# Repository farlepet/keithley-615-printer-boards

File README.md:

Keithley 615 Electrometer Printer Board Recreation
==================================================

This repo contains modern reproductions of the buffer/printer PCBs (PC209, PC218)
for the Keithley 615 electrometer.

Boards
------

 - PC218
   - Signal inverter/buffer board
   - Recreation of the origional PC218 schematic using modern SMD components is
     in the `PC218` directory
   - A simplified version using more modern ICs can be found in the `PC218v2` directory
 - PC209
   - Signal inverter/buffer and trigger board
   - Simplified version of the origional board can be found in the `PC209` directory
     - Same inverter/buffer scheme as PC218v2, with the origional trigger pulse
       generator and logic reduced down to discrete transistors, to simplify design.
 - Digital Interface Board
   - This will be a new board designed to connect to the 615 via the 50-pin
     Centronics connector
   - Planned features:
     - Passive data collection
     - Active triggering
     - USB-serial
     - RS-232 via DE-9
     - Ethernet

Photos
------

PC218 v2.2:

PC209 v1.0:

Interface/network board v1.0:

50-pin test board v1.0:

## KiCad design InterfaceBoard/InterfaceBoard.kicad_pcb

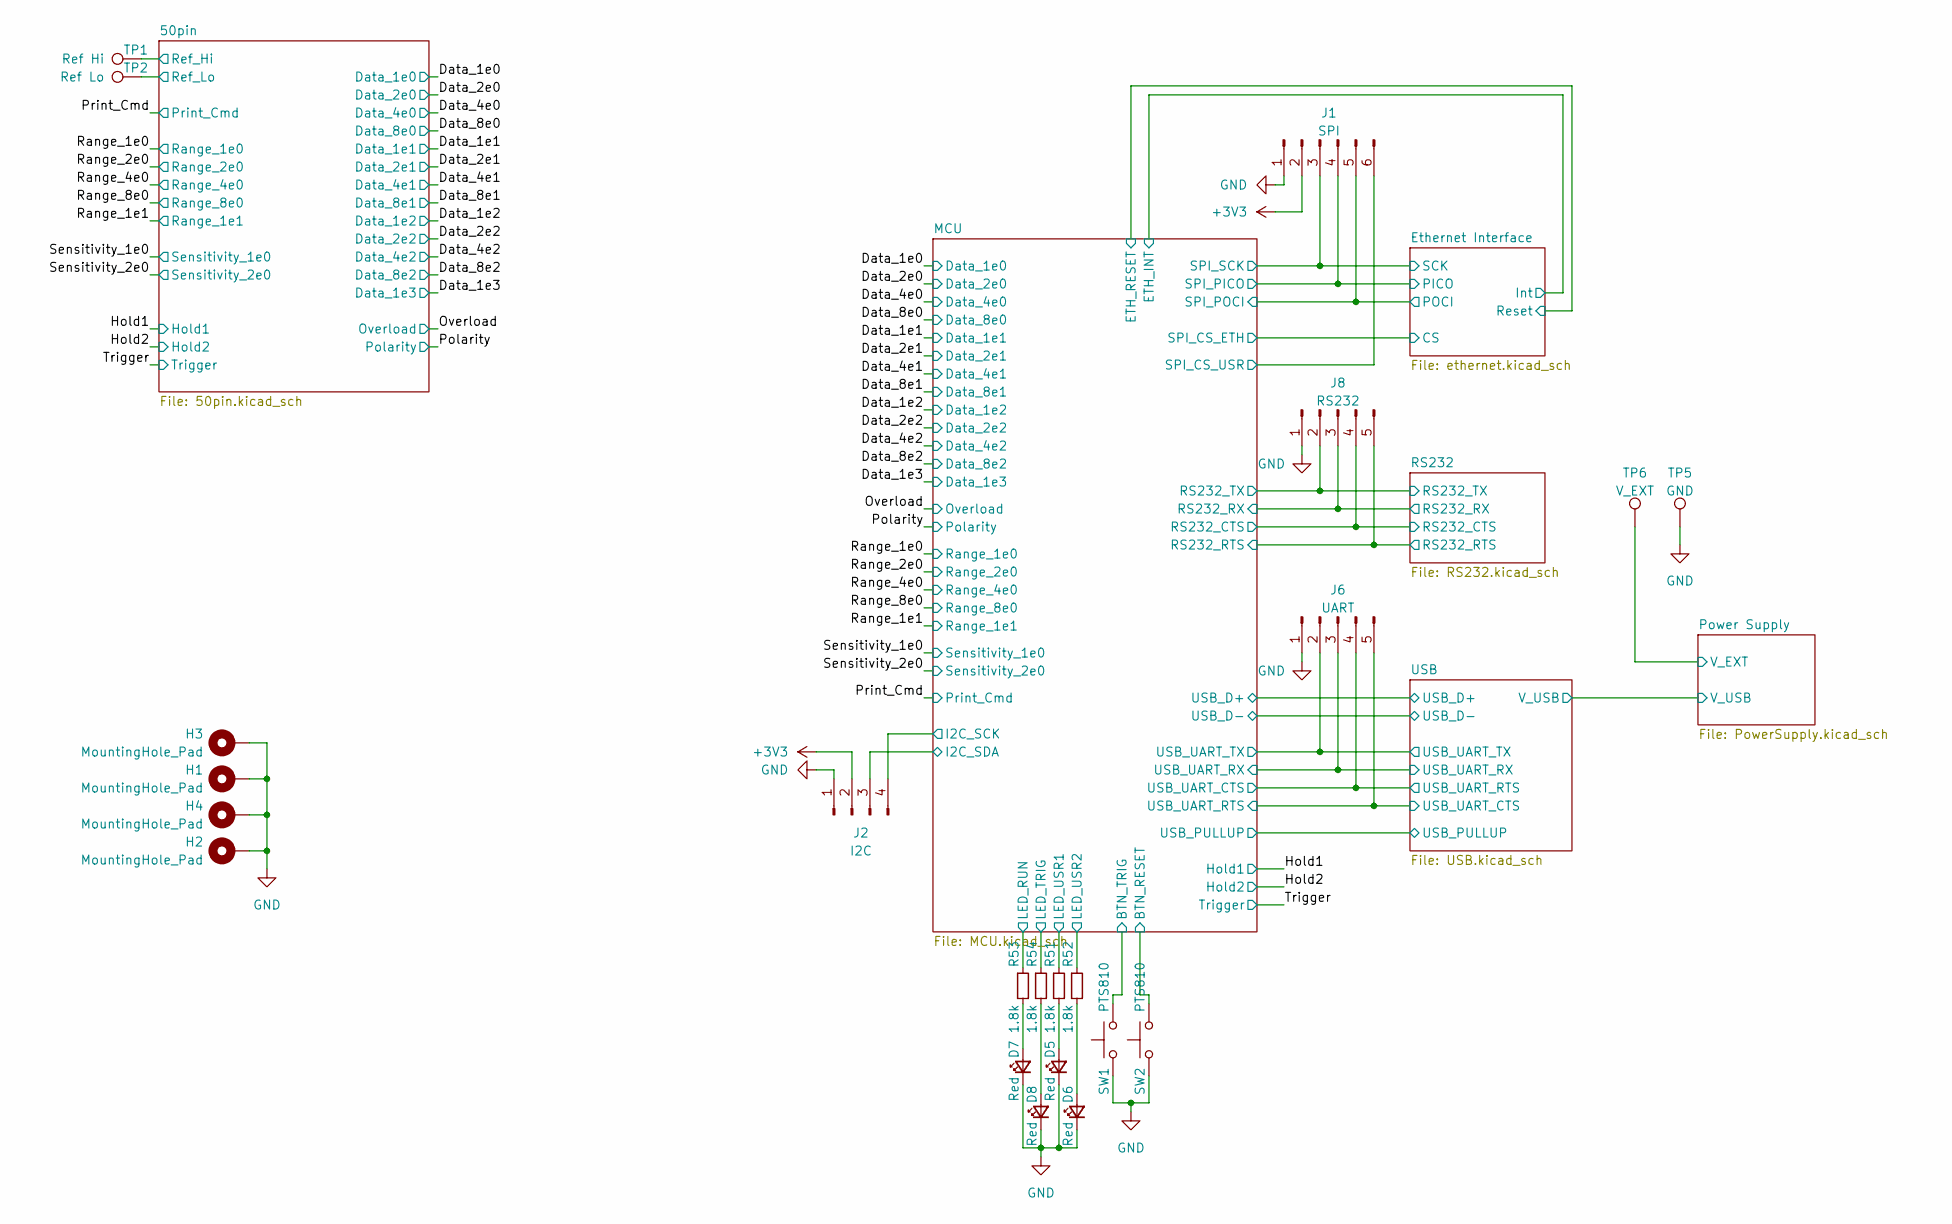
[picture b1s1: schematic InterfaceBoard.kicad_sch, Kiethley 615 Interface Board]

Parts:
D5, D6, D7, D8: Red; LED_0603_1608Metric
H1, H2, H3, H4: MountingHole_Pad; MountingHole_3.2mm_M3_Pad
J1: SPI; PinHeader_1x06_P1.27mm_Vertical
J2: I2C; PinHeader_1x04_P1.27mm_Vertical
J6: UART; PinHeader_1x05_P1.27mm_Vertical
J8: RS232; PinHeader_1x05_P1.27mm_Vertical
R51, R52, R53, R54: 1.8k; R_0603_1608Metric
SW1, SW2: PTS810; SW_SPST_PTS810
TP1: Ref Hi; TestPoint_Pad_1.5x1.5mm
TP2: Ref Lo; TestPoint_Pad_1.5x1.5mm
TP5: GND; TestPoint_THTPad_2.0x2.0mm_Drill1.0mm
TP6: V_EXT; TestPoint_THTPad_2.0x2.0mm_Drill1.0mm

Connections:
+3V3: J1.2, J2.2; also elsewhere on the board
/50pin/Ref_Hi: TP1.1; also elsewhere on the board
/50pin/Ref_Lo: TP2.1; also elsewhere on the board
/Ethernet Interface/PICO: J1.4; also elsewhere on the board
/Ethernet Interface/POCI: J1.5; also elsewhere on the board
/Ethernet Interface/SCK: J1.3; also elsewhere on the board
/MCU/BTN_TRIG: SW1.2; also elsewhere on the board
/MCU/I2C_SCK: J2.4; also elsewhere on the board
/MCU/I2C_SDA: J2.3; also elsewhere on the board
/MCU/LED_RUN: R53.1; also elsewhere on the board
/MCU/LED_TRIG: R54.1; also elsewhere on the board
/MCU/LED_USR1: R51.1; also elsewhere on the board
/MCU/LED_USR2: R52.1; also elsewhere on the board
/MCU/NRST: SW2.2; also elsewhere on the board
/MCU/RS232_CTS: J8.4; also elsewhere on the board
/MCU/RS232_RTS: J8.5; also elsewhere on the board
/MCU/RS232_RX: J8.3; also elsewhere on the board
/MCU/RS232_TX: J8.2; also elsewhere on the board
/MCU/SPI_CS_USR: J1.6; also elsewhere on the board
/MCU/USB_UART_CTS: J6.4; also elsewhere on the board
/MCU/USB_UART_RTS: J6.5; also elsewhere on the board
/MCU/USB_UART_RX: J6.3; also elsewhere on the board
/MCU/USB_UART_TX: J6.2; also elsewhere on the board
/Power Supply/V_EXT: TP6.1; also elsewhere on the board
GND: D5.1 (K), D6.1 (K), D7.1 (K), D8.1 (K), H1.1, H2.1, H3.1, H4.1, J1.1, J2.1, J6.1, J8.1, SW1.1, SW2.1, TP5.1; also elsewhere on the board
unnamed: D5.2 (A), R51.2
unnamed: D6.2 (A), R52.2
unnamed: D7.2 (A), R53.2
unnamed: D8.2 (A), R54.2

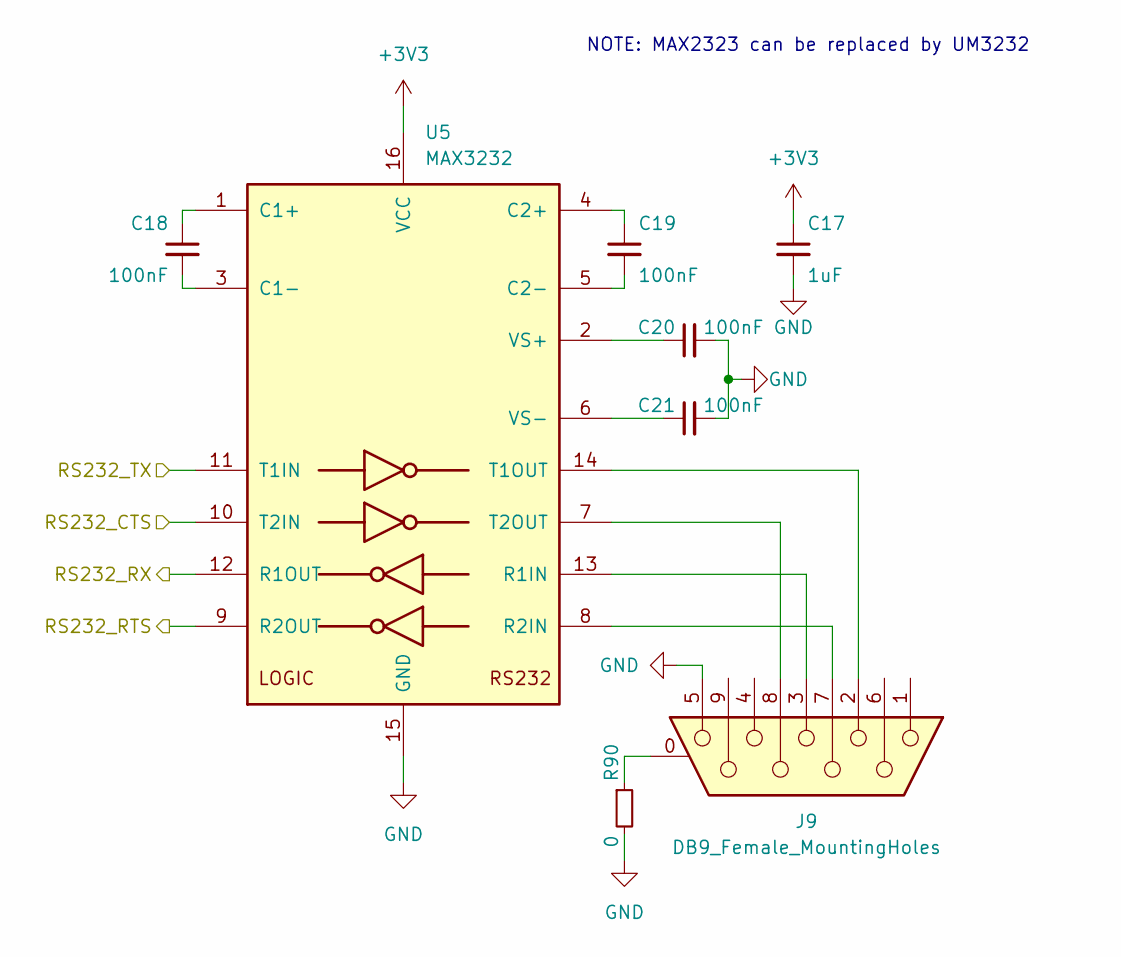
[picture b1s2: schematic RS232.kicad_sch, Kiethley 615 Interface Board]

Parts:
C17: 1uF; C_0603_1608Metric
C18, C19, C20, C21: 100nF; C_0603_1608Metric
J9: DB9_Female_MountingHoles; ASSMANN_A-DF_09_A_KG-T2S
R90: 0; R_0603_1608Metric
U5: MAX3232; SOIC-16_3.9x9.9mm_P1.27mm

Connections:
+3V3: C17.1, U5.16 (VCC); also elsewhere on the board
/MCU/RS232_CTS: U5.10 (T2IN); also elsewhere on the board
/MCU/RS232_RTS: U5.9 (R2OUT); also elsewhere on the board
/MCU/RS232_RX: U5.12 (R1OUT); also elsewhere on the board
/MCU/RS232_TX: U5.11 (T1IN); also elsewhere on the board
GND: C17.2, C20.2, C21.2, J9.5, R90.2, U5.15 (GND); also elsewhere on the board
unnamed: C18.1, U5.1 (C1+)
unnamed: C18.2, U5.3 (C1-)
unnamed: C19.1, U5.4 (C2+)
unnamed: C19.2, U5.5 (C2-)
unnamed: C20.1, U5.2 (VS+)
unnamed: C21.1, U5.6 (VS-)
unnamed: J9.0 (PAD), R90.1
unnamed: J9.2, U5.14 (T1OUT)
unnamed: J9.3, U5.13 (R1IN)
unnamed: J9.7, U5.8 (R2IN)
unnamed: J9.8, U5.7 (T2OUT)

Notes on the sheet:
NOTE: MAX2323 can be replaced by UM3232

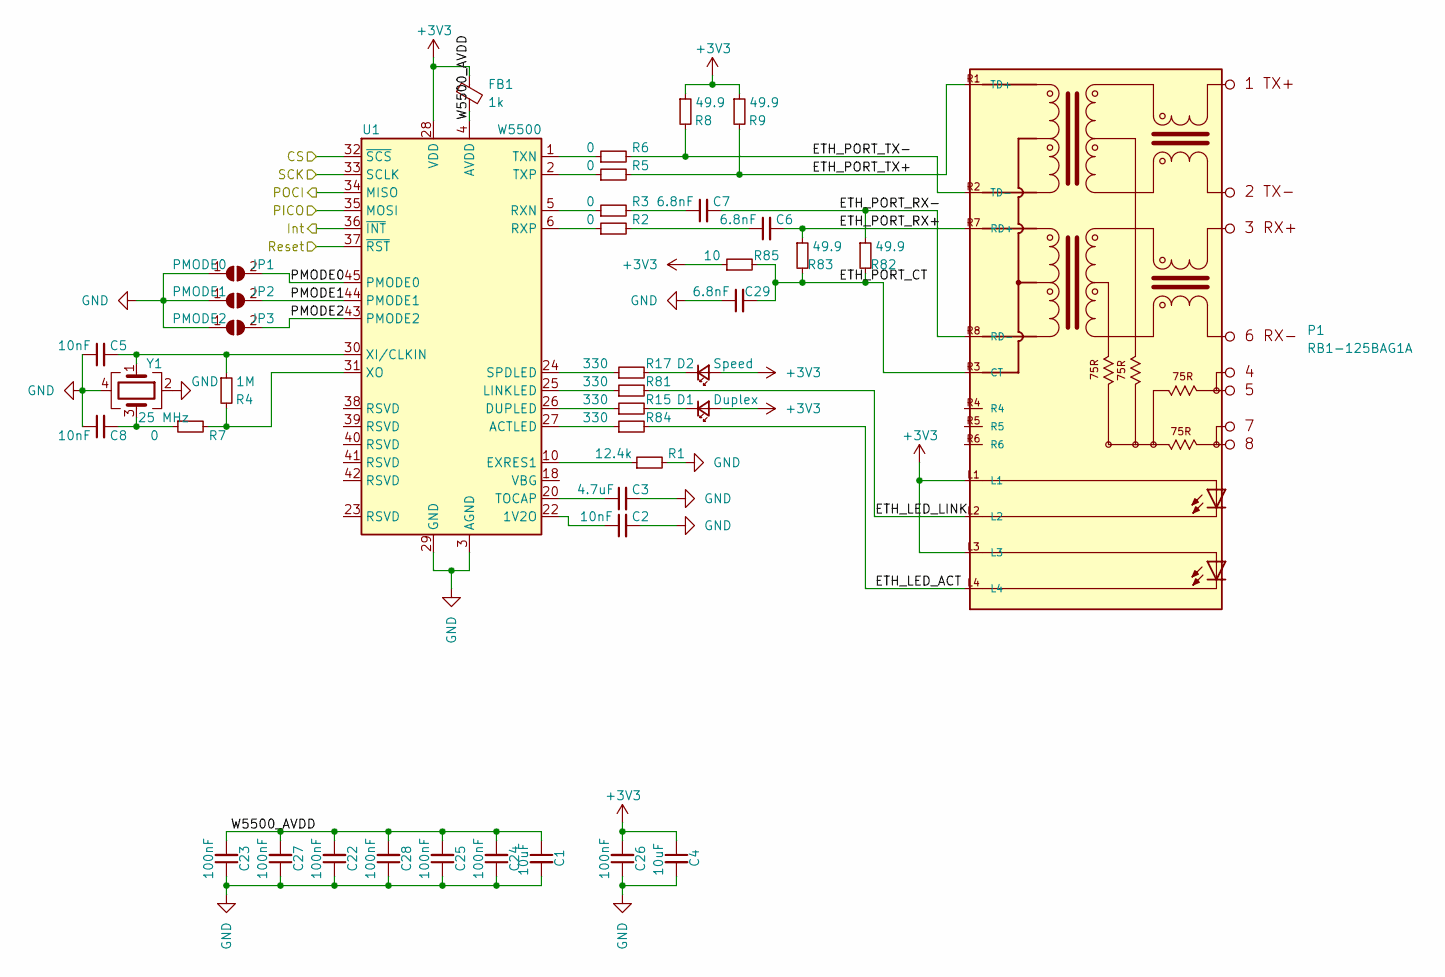
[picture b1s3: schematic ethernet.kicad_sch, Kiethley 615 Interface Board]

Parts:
C1, C4: 10uF; C_0805_2012Metric
C2, C5, C8: 10nF; C_0603_1608Metric
C3: 4.7uF; C_0603_1608Metric
C6, C7, C29: 6.8nF; C_0603_1608Metric
C22, C23, C24, C25, C26, C27, C28: 100nF; C_0603_1608Metric
D1: Duplex; LED_0603_1608Metric
D2: Speed; LED_0603_1608Metric
FB1: 1k; L_0805_2012Metric
JP1: PMODE0; 0603_solder_jumper
JP2: PMODE1; 0603_solder_jumper
JP3: PMODE2; 0603_solder_jumper
P1: RB1-125BAG1A; WIZNET_RB1-125BAG1A
R1: 12.4k; R_0603_1608Metric
R2, R3, R5, R6, R7: 0; R_0603_1608Metric
R4: 1M; R_0603_1608Metric
R8, R9, R82, R83: 49.9; R_0603_1608Metric
R15, R17, R81, R84: 330; R_0603_1608Metric
R85: 10; R_0603_1608Metric
U1: W5500; LQFP-48_7x7mm_P0.5mm
Y1: 25 MHz; Crystal_SMD_3225-4Pin_3.2x2.5mm

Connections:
+3V3: C4.1, C26.2, D1.2 (A), D2.2 (A), FB1.1, P1.L1, P1.L3, R8.1, R9.1, R85.1, U1.28 (VDD); also elsewhere on the board
/Ethernet Interface/CS: U1.32 (~SCS); also elsewhere on the board
/Ethernet Interface/ETH_LED_ACT: P1.L4, R84.2
/Ethernet Interface/ETH_LED_LINK: P1.L2, R81.2
/Ethernet Interface/ETH_PORT_CT: C29.2, P1.R3 (CT), R82.2, R83.2, R85.2
/Ethernet Interface/ETH_PORT_RX+: C6.2, P1.R7 (RD+), R83.1
/Ethernet Interface/ETH_PORT_RX-: C7.2, P1.R8 (RD-), R82.1
/Ethernet Interface/ETH_PORT_TX+: P1.R1 (TD+), R5.2, R9.2
/Ethernet Interface/ETH_PORT_TX-: P1.R2 (TD-), R6.2, R8.2
/Ethernet Interface/Int: U1.36 (~INT); also elsewhere on the board
/Ethernet Interface/PICO: U1.35 (MOSI); also elsewhere on the board
/Ethernet Interface/PMODE0: JP1.2 (B), U1.45 (PMODE0)
/Ethernet Interface/PMODE1: JP2.2 (B), U1.44 (PMODE1)
/Ethernet Interface/PMODE2: JP3.2 (B), U1.43 (PMODE2)
/Ethernet Interface/POCI: U1.34 (MISO); also elsewhere on the board
/Ethernet Interface/Reset: U1.37 (~RST); also elsewhere on the board
/Ethernet Interface/SCK: U1.33 (SCLK); also elsewhere on the board
/Ethernet Interface/W5500_AVDD: C1.1, C22.2, C23.2, C24.2, C25.2, C27.2, C28.2, FB1.2, U1.4 (AVDD), U1.8 (AVDD), U1.11 (AVDD), U1.15 (AVDD), U1.17 (AVDD), U1.21 (AVDD)
GND: C1.2, C2.2, C3.2, C4.2, C5.1, C8.1, C22.1, C23.1, C24.1, C25.1, C26.1, C27.1, C28.1, C29.1, JP1.1 (A), JP2.1 (A), JP3.1 (A), R1.2, U1.3 (AGND), U1.9 (AGND), U1.14 (AGND), U1.16 (AGND), U1.19 (AGND), U1.29 (GND), U1.48 (AGND), Y1.2, Y1.4; also elsewhere on the board
unnamed: C2.1, U1.22 (1V2O)
unnamed: C3.1, U1.20 (TOCAP)
unnamed: C5.2, R4.1, U1.30 (XI/CLKIN), Y1.1
unnamed: C6.1, R2.2
unnamed: C7.1, R3.2
unnamed: C8.2, R7.1, Y1.3
unnamed: D1.1 (K), R15.2
unnamed: D2.1 (K), R17.2
unnamed: R1.1, U1.10 (EXRES1)
unnamed: R2.1, U1.6 (RXP)
unnamed: R3.1, U1.5 (RXN)
unnamed: R4.2, R7.2, U1.31 (XO)
unnamed: R5.1, U1.2 (TXP)
unnamed: R6.1, U1.1 (TXN)
unnamed: R15.1, U1.26 (DUPLED)
unnamed: R17.1, U1.24 (SPDLED)
unnamed: R81.1, U1.25 (LINKLED)
unnamed: R84.1, U1.27 (ACTLED)

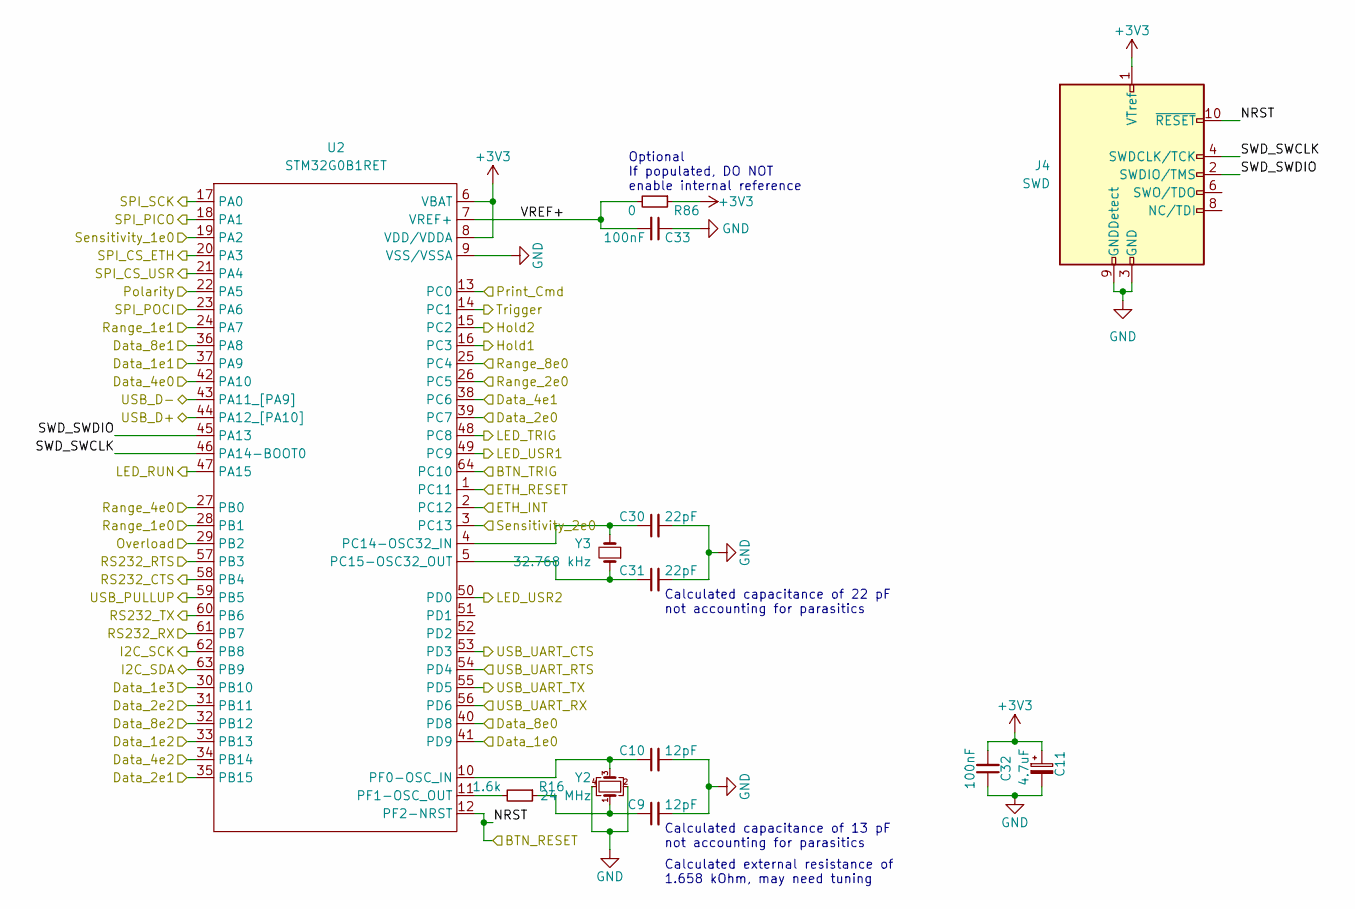
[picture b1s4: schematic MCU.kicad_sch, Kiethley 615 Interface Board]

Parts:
C9, C10: 12pF; C_0603_1608Metric
C11: 4.7uF; CP_Elec_5x5.9
C30, C31: 22pF; C_0603_1608Metric
C32, C33: 100nF; C_0603_1608Metric
J4: SWD; PinHeader_2x05_P1.27mm_Vertical
R16: 1.6k; R_0603_1608Metric
R86: 0; R_0603_1608Metric
U2: STM32G0B1RET; LQFP-64_10x10mm_P0.5mm
Y2: 24 MHz; Crystal_SMD_3225-4Pin_3.2x2.5mm
Y3: 32.768 kHz; Crystal_C26-LF_D2.1mm_L6.5mm_Horizontal

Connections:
+3V3: C11.1, C32.2, J4.1 (VTref), R86.1, U2.6 (VBAT), U2.8 (VDD/VDDA); also elsewhere on the board
/Data_1e0: U2.41 (PD9); also elsewhere on the board
/Data_1e1: U2.37 (PA9); also elsewhere on the board
/Data_1e2: U2.33 (PB13); also elsewhere on the board
/Data_1e3: U2.30 (PB10); also elsewhere on the board
/Data_2e0: U2.39 (PC7); also elsewhere on the board
/Data_2e1: U2.35 (PB15); also elsewhere on the board
/Data_2e2: U2.31 (PB11); also elsewhere on the board
/Data_4e0: U2.42 (PA10); also elsewhere on the board
/Data_4e1: U2.38 (PC6); also elsewhere on the board
/Data_4e2: U2.34 (PB14); also elsewhere on the board
/Data_8e0: U2.40 (PD8); also elsewhere on the board
/Data_8e1: U2.36 (PA8); also elsewhere on the board
/Data_8e2: U2.32 (PB12); also elsewhere on the board
/Ethernet Interface/CS: U2.20 (PA3); also elsewhere on the board
/Ethernet Interface/Int: U2.2 (PC12); also elsewhere on the board
/Ethernet Interface/PICO: U2.18 (PA1); also elsewhere on the board
/Ethernet Interface/POCI: U2.23 (PA6); also elsewhere on the board
/Ethernet Interface/Reset: U2.1 (PC11); also elsewhere on the board
/Ethernet Interface/SCK: U2.17 (PA0); also elsewhere on the board
/Hold1: U2.16 (PC3); also elsewhere on the board
/Hold2: U2.15 (PC2); also elsewhere on the board
/MCU/BTN_TRIG: U2.64 (PC10); also elsewhere on the board
/MCU/I2C_SCK: U2.62 (PB8); also elsewhere on the board
/MCU/I2C_SDA: U2.63 (PB9); also elsewhere on the board
/MCU/LED_RUN: U2.47 (PA15); also elsewhere on the board
/MCU/LED_TRIG: U2.48 (PC8); also elsewhere on the board
/MCU/LED_USR1: U2.49 (PC9); also elsewhere on the board
/MCU/LED_USR2: U2.50 (PD0); also elsewhere on the board
/MCU/NRST: J4.10 (~RESET), U2.12 (PF2-NRST); also elsewhere on the board
/MCU/RS232_CTS: U2.58 (PB4); also elsewhere on the board
/MCU/RS232_RTS: U2.57 (PB3); also elsewhere on the board
/MCU/RS232_RX: U2.61 (PB7); also elsewhere on the board
/MCU/RS232_TX: U2.60 (PB6); also elsewhere on the board
/MCU/SPI_CS_USR: U2.21 (PA4); also elsewhere on the board
/MCU/SWD_SWCLK: J4.4 (SWDCLK/TCK), U2.46 (PA14-BOOT0)
/MCU/SWD_SWDIO: J4.2 (SWDIO/TMS), U2.45 (PA13)
/MCU/USB_D+: U2.44 (PA12_[PA10]); also elsewhere on the board
/MCU/USB_D-: U2.43 (PA11_[PA9]); also elsewhere on the board
/MCU/USB_PULLUP: U2.59 (PB5); also elsewhere on the board
/MCU/USB_UART_CTS: U2.53 (PD3); also elsewhere on the board
/MCU/USB_UART_RTS: U2.54 (PD4); also elsewhere on the board
/MCU/USB_UART_RX: U2.56 (PD6); also elsewhere on the board
/MCU/USB_UART_TX: U2.55 (PD5); also elsewhere on the board
/MCU/VREF+: C33.2, R86.2, U2.7 (VREF+)
/Overload: U2.29 (PB2); also elsewhere on the board
/Polarity: U2.22 (PA5); also elsewhere on the board
/Print_Cmd: U2.13 (PC0); also elsewhere on the board
/Range_1e0: U2.28 (PB1); also elsewhere on the board
/Range_1e1: U2.24 (PA7); also elsewhere on the board
/Range_2e0: U2.26 (PC5); also elsewhere on the board
/Range_4e0: U2.27 (PB0); also elsewhere on the board
/Range_8e0: U2.25 (PC4); also elsewhere on the board
/Sensitivity_1e0: U2.19 (PA2); also elsewhere on the board
/Sensitivity_2e0: U2.3 (PC13); also elsewhere on the board
/Trigger: U2.14 (PC1); also elsewhere on the board
GND: C9.2, C10.2, C11.2, C30.2, C31.2, C32.1, C33.1, J4.3 (GND), J4.5 (GND), J4.9 (GNDDetect), U2.9 (VSS/VSSA), Y2.2, Y2.4; also elsewhere on the board
unnamed: C9.1, R16.1, Y2.1
unnamed: C10.1, U2.10 (PF0-OSC_IN), Y2.3
unnamed: C30.1, U2.4 (PC14-OSC32_IN), Y3.2
unnamed: C31.1, U2.5 (PC15-OSC32_OUT), Y3.1
unnamed: R16.2, U2.11 (PF1-OSC_OUT)

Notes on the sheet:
Calculated external resistance of 1.658 kOhm, may need tuning
Calculated capacitance of 13 pF not accounting for parasitics
Calculated capacitance of 22 pF not accounting for parasitics
Optional If populated, DO NOT enable internal reference

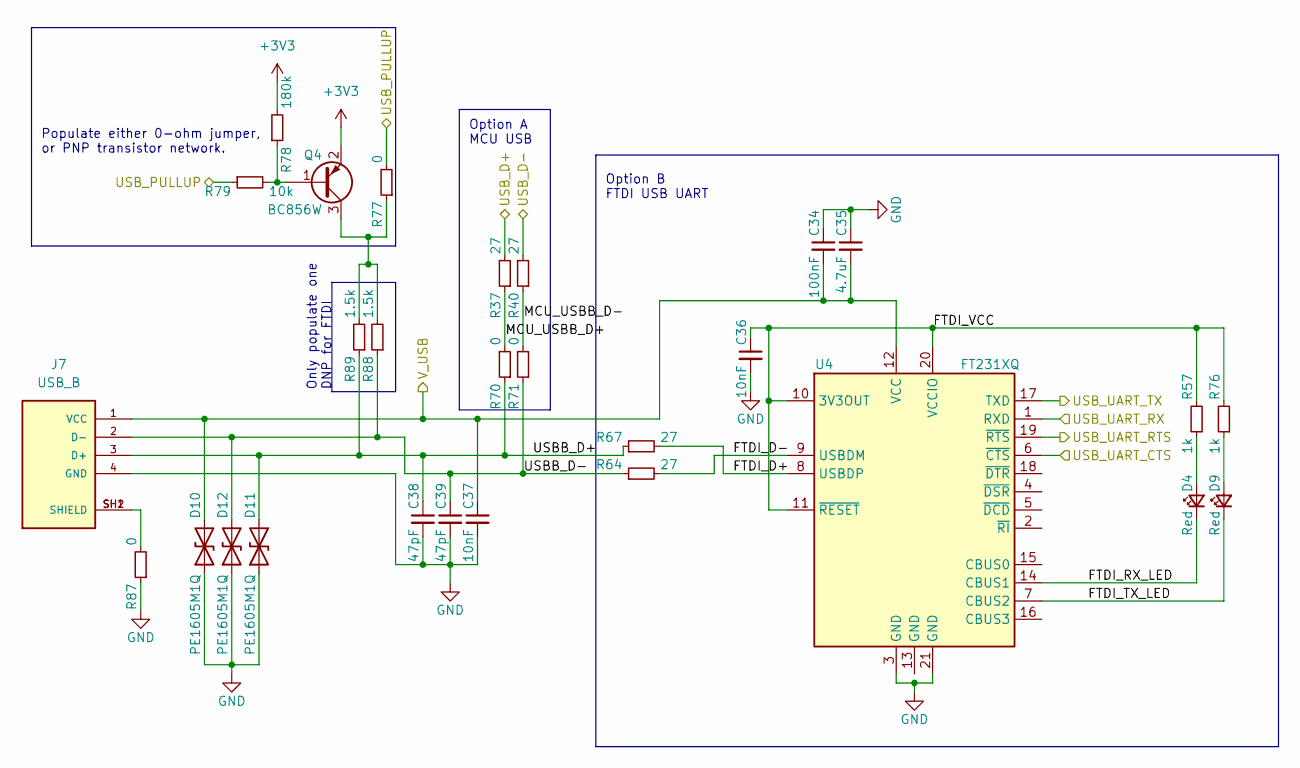
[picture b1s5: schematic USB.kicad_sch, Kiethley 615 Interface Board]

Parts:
C34: 100nF; C_0603_1608Metric
C35: 4.7uF; C_0603_1608Metric
C36, C37: 10nF; C_0603_1608Metric
C38, C39: 47pF; C_0603_1608Metric
D4, D9: Red; LED_0603_1608Metric
D10, D11, D12: PE1605M1Q; D_0402_1005Metric
J7: USB_B; CUI_UJ2-BH-W1-TH; PART_REV 1.0
Q4: BC856W; SOT-323_SC-70
R37, R40, R64, R67: 27; R_0603_1608Metric
R57, R76: 1k; R_0603_1608Metric
R70, R71, R77, R87: 0; R_0603_1608Metric
R78: 180k; R_0603_1608Metric
R79: 10k; R_0603_1608Metric
R88, R89: 1.5k; R_0603_1608Metric
U4: FT231XQ; QFN-20-1EP_4x4mm_P0.5mm_EP2.5x2.5mm

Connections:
+3V3: Q4.2 (E), R78.2; also elsewhere on the board
/MCU/USB_D+: R37.2; also elsewhere on the board
/MCU/USB_D-: R40.2; also elsewhere on the board
/MCU/USB_PULLUP: R77.2, R79.1; also elsewhere on the board
/MCU/USB_UART_CTS: U4.19 (~RTS); also elsewhere on the board
/MCU/USB_UART_RTS: U4.6 (~CTS); also elsewhere on the board
/MCU/USB_UART_RX: U4.1 (RXD); also elsewhere on the board
/MCU/USB_UART_TX: U4.17 (TXD); also elsewhere on the board
/Power Supply/V_USB: C34.2, C35.2, C37.1, D10.2 (A2), J7.1 (VCC), U4.12 (VCC); also elsewhere on the board
/USB/FTDI_D+: R67.2, U4.8 (USBDP)
/USB/FTDI_D-: R64.2, U4.9 (USBDM)
/USB/FTDI_RX_LED: D4.1 (K), U4.14 (CBUS1)
/USB/FTDI_TX_LED: D9.1 (K), U4.7 (CBUS2)
/USB/FTDI_VCC: C36.1, R57.2, R76.2, U4.10 (3V3OUT), U4.11 (~RESET), U4.20 (VCCIO)
/USB/MCU_USBB_D+: R37.1, R70.2
/USB/MCU_USBB_D-: R40.1, R71.2
/USB/USBB_D+: C38.1, D11.2 (A2), J7.3 (D+), R67.1, R70.1, R89.1
/USB/USBB_D-: C39.1, D12.2 (A2), J7.2 (D-), R64.1, R71.1, R88.1
GND: C34.1, C35.1, C36.2, C37.2, C38.2, C39.2, D10.1 (A1), D11.1 (A1), D12.1 (A1), J7.4 (GND), R87.1, U4.3 (GND), U4.21 (GND); also elsewhere on the board
unnamed: D4.2 (A), R57.1
unnamed: D9.2 (A), R76.1
unnamed: J7.SH1 (SHIELD), J7.SH2 (SHIELD), R87.2
unnamed: Q4.1 (B), R78.1, R79.2
unnamed: Q4.3 (C), R77.1, R88.2, R89.2

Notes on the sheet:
Option A MCU USB
Populate either 0-ohm jumper, or PNP transistor network.
Option B FTDI USB UART
Only populate one DNP for FTDI

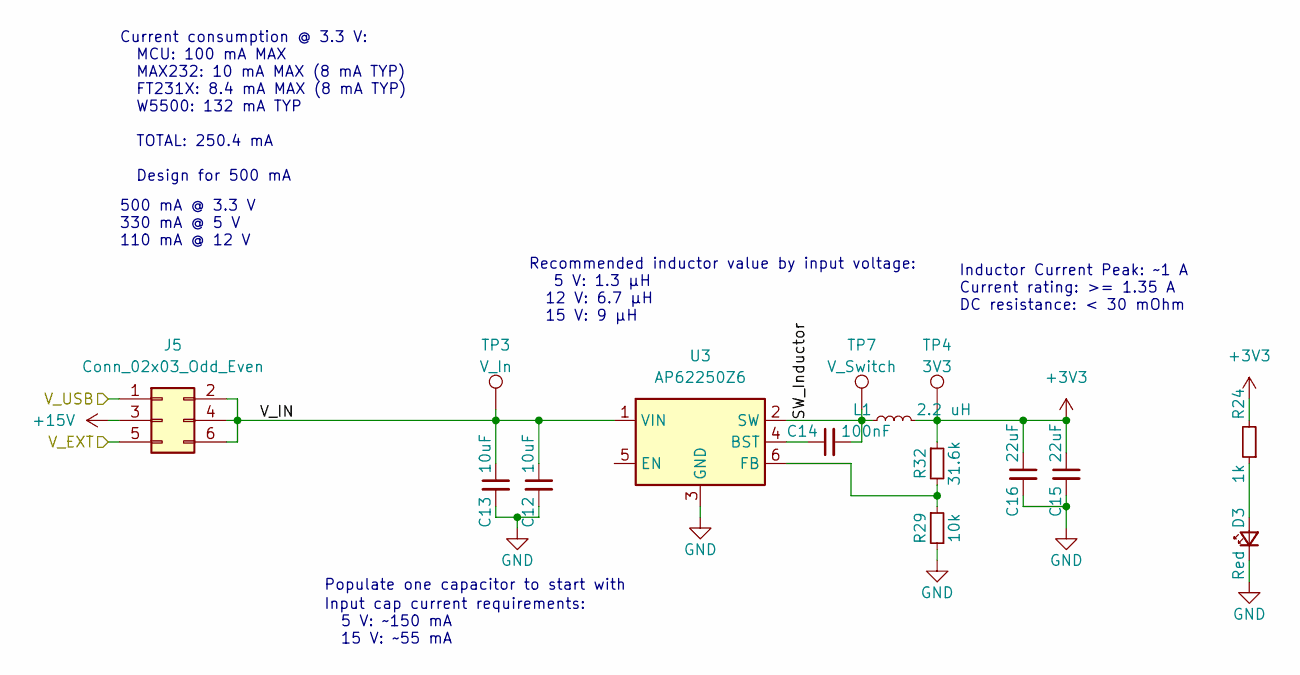
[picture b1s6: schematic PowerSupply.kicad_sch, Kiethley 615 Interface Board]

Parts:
C12, C13: 10uF; C_0805_2012Metric
C14: 100nF; C_0603_1608Metric
C15, C16: 22uF; C_0805_2012Metric
D3: Red; LED_0603_1608Metric
J5: Conn_02x03_Odd_Even; PinHeader_2x03_P1.27mm_Vertical
L1: 2.2 uH; L_Taiyo-Yuden_NR-50xx
R24: 1k; R_0603_1608Metric
R29: 10k; R_0603_1608Metric
R32: 31.6k; R_0603_1608Metric
TP3: V_In; TestPoint_THTPad_1.5x1.5mm_Drill0.7mm
TP4: 3V3; TestPoint_THTPad_1.5x1.5mm_Drill0.7mm
TP7: V_Switch; TestPoint_THTPad_1.5x1.5mm_Drill0.7mm
U3: AP62250Z6; SOT-563

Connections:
+3V3: C15.1, C16.1, L1.2, R24.2, R32.1, TP4.1; also elsewhere on the board
+15V: J5.3; also elsewhere on the board
/Power Supply/SW_Inductor: C14.2, L1.1, TP7.1, U3.2 (SW)
/Power Supply/V_EXT: J5.5; also elsewhere on the board
/Power Supply/V_IN: C12.1, C13.1, J5.2, J5.4, J5.6, TP3.1, U3.1 (VIN)
/Power Supply/V_USB: J5.1; also elsewhere on the board
GND: C12.2, C13.2, C15.2, C16.2, D3.1 (K), R29.2, U3.3 (GND); also elsewhere on the board
unnamed: C14.1, U3.4 (BST)
unnamed: D3.2 (A), R24.1
unnamed: R29.1, R32.2, U3.6 (FB)

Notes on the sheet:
Input cap current requirements: 5 V: ~150 mA 15 V: ~55 mA
Current consumption @ 3.3 V: MCU: 100 mA MAX MAX232: 10 mA MAX (8 mA TYP) FT231X: 8.4 mA MAX (8 mA TYP) W5500: 132 mA TYP TOTAL: 250.4 mA Design for 500 mA
Inductor Current Peak: ~1 A Current rating: >= 1.35 A DC resistance: < 30 mOhm
500 mA @ 3.3 V 330 mA @ 5 V 110 mA @ 12 V
Recommended inductor value by input voltage: 5 V: 1.3 µH 12 V: 6.7 µH 15 V: 9 µH
Populate one capacitor to start with

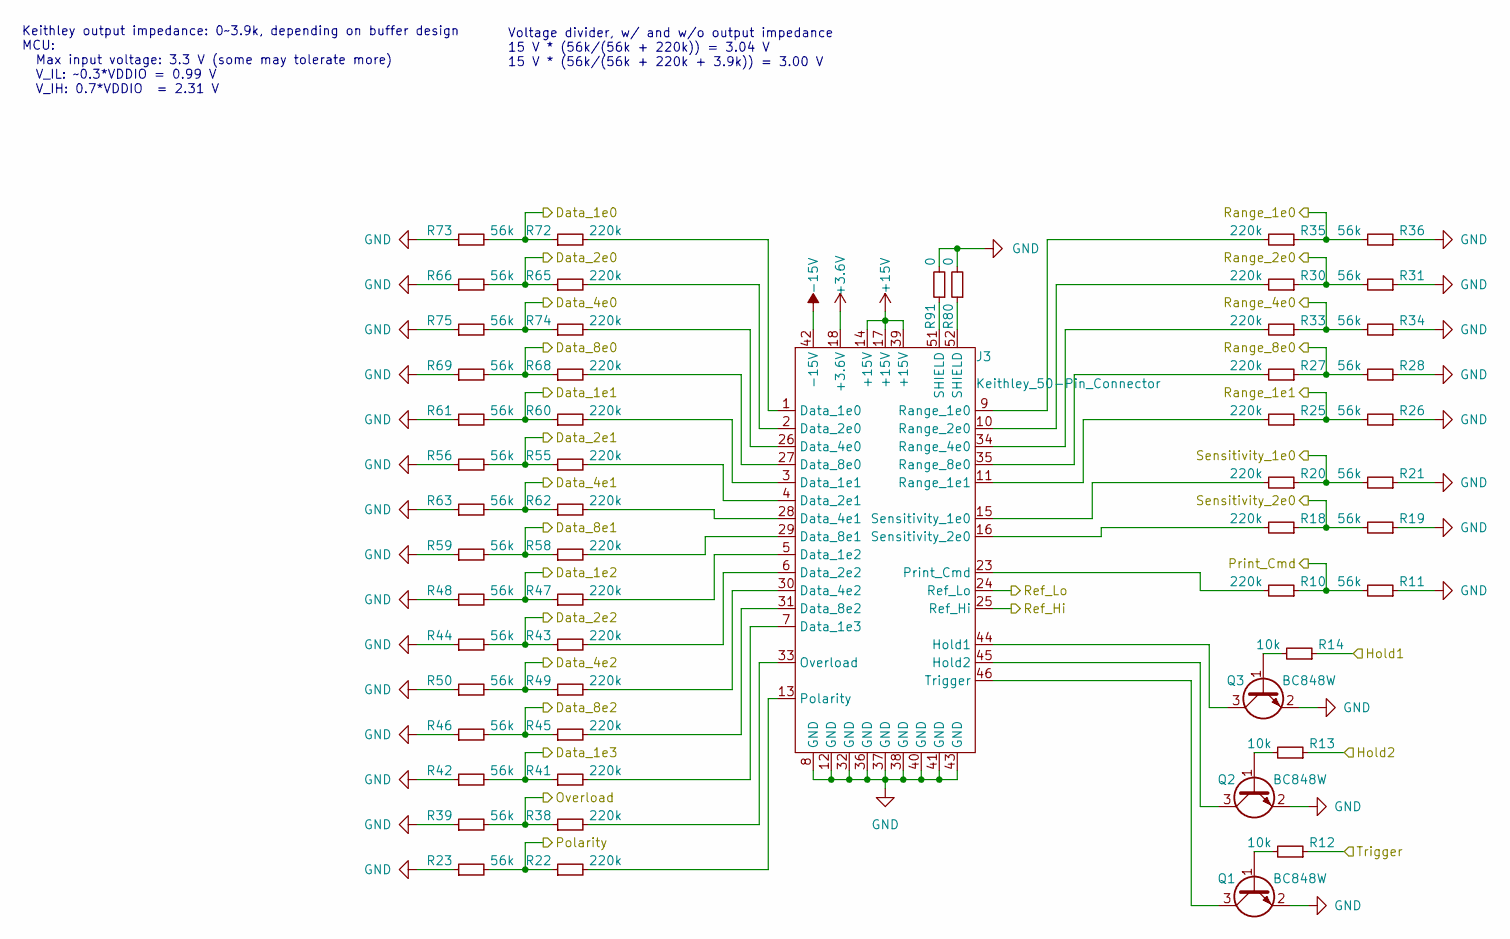
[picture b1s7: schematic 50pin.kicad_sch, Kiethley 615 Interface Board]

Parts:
J3: Keithley_50-Pin_Connector; NorComp_112-050-213R001
Q1, Q2, Q3: BC848W; SOT-323_SC-70
R10, R18, R20, R22, R25, R27, R30, R33, R35, R38, R41, R43, R45, R47, R49, R55, R58, R60, R62, R65, R68, R72, R74: 220k; R_0603_1608Metric
R11, R19, R21, R23, R26, R28, R31, R34, R36, R39, R42, R44, R46, R48, R50, R56, R59, R61, R63, R66, R69, R73, R75: 56k; R_0603_1608Metric
R12, R13, R14: 10k; R_0603_1608Metric
R80, R91: 0; R_0603_1608Metric

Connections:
+3.6V: J3.18 (+3.6V)
+15V: J3.14 (+15V), J3.17 (+15V), J3.39 (+15V); also elsewhere on the board
-15V: J3.42 (-15V)
/50pin/Ref_Hi: J3.25 (Ref_Hi); also elsewhere on the board
/50pin/Ref_Lo: J3.24 (Ref_Lo); also elsewhere on the board
/Data_1e0: R72.1, R73.2; also elsewhere on the board
/Data_1e1: R60.1, R61.2; also elsewhere on the board
/Data_1e2: R47.1, R48.2; also elsewhere on the board
/Data_1e3: R41.1, R42.2; also elsewhere on the board
/Data_2e0: R65.1, R66.2; also elsewhere on the board
/Data_2e1: R55.1, R56.2; also elsewhere on the board
/Data_2e2: R43.1, R44.2; also elsewhere on the board
/Data_4e0: R74.1, R75.2; also elsewhere on the board
/Data_4e1: R62.1, R63.2; also elsewhere on the board
/Data_4e2: R49.1, R50.2; also elsewhere on the board
/Data_8e0: R68.1, R69.2; also elsewhere on the board
/Data_8e1: R58.1, R59.2; also elsewhere on the board
/Data_8e2: R45.1, R46.2; also elsewhere on the board
/Hold1: R14.1; also elsewhere on the board
/Hold2: R13.1; also elsewhere on the board
/Overload: R38.1, R39.2; also elsewhere on the board
/Polarity: R22.1, R23.2; also elsewhere on the board
/Print_Cmd: R10.1, R11.2; also elsewhere on the board
/Range_1e0: R35.1, R36.2; also elsewhere on the board
/Range_1e1: R25.1, R26.2; also elsewhere on the board
/Range_2e0: R30.1, R31.2; also elsewhere on the board
/Range_4e0: R33.1, R34.2; also elsewhere on the board
/Range_8e0: R27.1, R28.2; also elsewhere on the board
/Sensitivity_1e0: R20.1, R21.2; also elsewhere on the board
/Sensitivity_2e0: R18.1, R19.2; also elsewhere on the board
/Trigger: R12.1; also elsewhere on the board
GND: J3.8 (GND), J3.12 (GND), J3.32 (GND), J3.36 (GND), J3.37 (GND), J3.38 (GND), J3.40 (GND), J3.41 (GND), J3.43 (GND), Q1.2 (E), Q2.2 (E), Q3.2 (E), R11.1, R19.1, R21.1, R23.1, R26.1, R28.1, R31.1, R34.1, R36.1, R39.1, R42.1, R44.1, R46.1, R48.1, R50.1, R56.1, R59.1, R61.1, R63.1, R66.1, R69.1, R73.1, R75.1, R80.2, R91.2; also elsewhere on the board
unnamed: J3.1 (Data_1e0), R72.2
unnamed: J3.2 (Data_2e0), R65.2
unnamed: J3.3 (Data_1e1), R60.2
unnamed: J3.4 (Data_2e1), R55.2
unnamed: J3.5 (Data_1e2), R47.2
unnamed: J3.6 (Data_2e2), R43.2
unnamed: J3.7 (Data_1e3), R41.2
unnamed: J3.9 (Range_1e0), R35.2
unnamed: J3.10 (Range_2e0), R30.2
unnamed: J3.11 (Range_1e1), R25.2
unnamed: J3.13 (Polarity), R22.2
unnamed: J3.15 (Sensitivity_1e0), R20.2
unnamed: J3.16 (Sensitivity_2e0), R18.2
unnamed: J3.23 (Print_Cmd), R10.2
unnamed: J3.26 (Data_4e0), R74.2
unnamed: J3.27 (Data_8e0), R68.2
unnamed: J3.28 (Data_4e1), R62.2
unnamed: J3.29 (Data_8e1), R58.2
unnamed: J3.30 (Data_4e2), R49.2
unnamed: J3.31 (Data_8e2), R45.2
unnamed: J3.33 (Overload), R38.2
unnamed: J3.34 (Range_4e0), R33.2
unnamed: J3.35 (Range_8e0), R27.2
unnamed: J3.44 (Hold1), Q3.3 (C)
unnamed: J3.45 (Hold2), Q2.3 (C)
unnamed: J3.46 (Trigger), Q1.3 (C)
unnamed: J3.51 (SHIELD), R91.1
unnamed: J3.52 (SHIELD), R80.1
unnamed: Q1.1 (B), R12.2
unnamed: Q2.1 (B), R13.2
unnamed: Q3.1 (B), R14.2

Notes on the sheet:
Voltage divider, w/ and w/o output impedance 15 V * (56k/(56k + 220k)) = 3.04 V 15 V * (56k/(56k + 220k + 3.9k)) = 3.00 V
Keithley output impedance: 0~3.9k, depending on buffer design MCU: Max input voltage: 3.3 V (some may tolerate more) V_IL: ~0.3*VDDIO = 0.99 V V_IH: 0.7*VDDIO = 2.31 V
